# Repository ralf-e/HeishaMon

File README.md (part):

# HeishaMon mit Touch-Display

Dieser Fork ergänzt **HeishaMon Large / V6 (ESP32-S3)** um ein lokales Touch-Display. Die Erweiterung liegt auf dem Branch `touch-display`; `main` bleibt beim offiziellen HeishaMon-Stand.

- **Anzeige:** Waveshare 3,5-Zoll-IPS-Display (SKU 29318), 480 × 320 Pixel im Querformat. Die Übersicht zeigt 20 Werte, darunter Vorlauf/Rücklauf, Warmwasser und Heizkreise mit Ist-/Sollwerten, Volumenstrom und Wärmepumpenstatus.
- **Bedienung:** Per Touch durch alle WP-Topics, Zusatzdaten, Optional-PCB-Werte und Dallas-Sensoren blättern. Antippen öffnet Wertdetails; die Geräteinfo zeigt Modell- und Firmwaredaten. Fehlende und veraltete Daten werden gekennzeichnet.
- **Betriebsart:** „Automatisch“ oder „Listen only“ direkt am Display wählen und dauerhaft speichern. Bestehende Web-Einstellungen und Empfangsprüfungen bleiben wirksam. Das Display selbst erzeugt keine Wärmepumpen-Stellbefehle.
- **Aufbau:** Eine eigene Adapterplatine Rev.0.6 verbindet das Display mit der V6; optionales W5500-Ethernet ist weiterhin vorgesehen. Schaltplan, KiCad-Projekt und Fertigungsdaten liegen bei.

**Stand:** Software `0.1.0-dev.7`; [ESP32-S3-Build und Regressionstests erfolgreich](https://github.com/ralf-e/HeishaMon/actions/runs/40380596372). Hardwaretests, Passform und Stromreserve an der realen V6 stehen noch aus; die Firmware ist ein Entwicklungsstand.

**Weiterlesen:** [Touch-Dokumentation und Vorschau](touch-extension/README.md) · [Build, Installation und Updates im Fork](touch-extension/docs/Fork_Workflow.md)

**Neue Hardwarevariante:** [Adapter Rev.0.7 mit vier Spannungsmessungen](touch-extension/hardware/Rev07/README.md), weiterhin 23 × 41 mm. Rev.0.6 bleibt erhalten; die bisherige dev.7-Firmware wertet den neuen ADC noch nicht aus.

**Lizenz:** Die eigene Touch-Erweiterungssoftware steht unter [MPL-2.0](touch-extension/LICENSE); Geltungsbereich und Ausnahmen stehen in [LICENSING.md](touch-extension/LICENSING.md). Für HeishaMon selbst schlägt Upstream als Antwort auf [Issue #1029](https://github.com/heishamon/HeishaMon/issues/1029#issuecomment-6421009129) in [PR #1030](https://github.com/heishamon/HeishaMon/pull/1030) MPL-2.0 samt Drittlizenzhinweisen vor. Stand 26.10.2026 ist der PR noch offen. Einzelheiten stehen in den [Lizenzhinweisen zum Fork](touch-extension/docs/Fork_Workflow.md#prüfumfang-und-lizenz).

---

Die ursprüngliche HeishaMon-README folgt unten.

# Panasonic H, J, K & L Series Aquarea air-water heat pump protocol

This project makes it possible to read information from Panasonic Aquarea heat pump and report the data either to an MQTT server or as JSON format over HTTP.

Eine deutschsprachige [README_DE.md](README_DE.md) findest du hier. \
Een nederlandse vertaling [README_NL.md](README_NL.md) vind je hier. \
Suomen kielellä [README_FI.md](README_FI.md) luettavissa täällä.

*Help on translation to other languages is welcome.*

# Current releases
Latest release is available [here](https://github.com/Egyras/HeishaMon/releases). The ESP8266 compiled binary can be installed on a Wemos D1 mini, on the HeishaMon PCB and generally on any ESP8266 based board compatible with Wemos build settings (at least 4MB flash). You can also download the code and compile it yourself (see required libraries below). The ESP32-S3 binary is for the newer, large, version of heishamon.

# Using the software
HeishaMon is able to communicate with the Panasonic Aquarea H, J, K and L&series. [Confirmed by users types of HP you can find here](HeatPumpType.md) \
If you want to compile this image yourself be sure to use the mentioned libraries and support for a filesystem on the esp8266 so select the correct flash option in arduino ide for that.

When starting, without a configured wifi, an open-wifi-hotspot will be visible allowing you to configure your wifi network and your MQTT server. Configuration page will be located at http://192.168.4.1 . \

After configuring and booting the image will be able to read and talk to your heatpump. The GPIO13/GPIO15 connection will be used for communications so you can keep your computer/uploader connected to the board if you want. \
Serial 1 (GPIO2) can be used to connect another serial line (GND and TX from the board only) to read some debugging data.

All received data will be sent to different MQTT topics (see below for topic descriptions). There is also a 'panasonic_heat_pump/log' MQTT topic which provides debug logging and a hexdump of the received packets (if enabled in the web portal).

Some heatpumps (K/L series and newer) also send an additional "extra data block" with separate, more precise power consumption/production values. HeishaMon detects this automatically at boot and, if supported, publishes these as XTOP topics under 'panasonic_heat_pump/extra/...' (see [MQTT-Topics.md](MQTT-Topics.md) for the full list). If your heatpump doesn't support this extra data block, these topics simply won't appear. Note that on heatpumps that do support it, the "old" power topics (TOP15/16, TOP38-41, see MQTT-Topics.md) are no longer populated by the heatpump and will report bogus/invalid values (e.g. -200) — use the XTOP power values instead in that case.

You can connect a 1wire network on GPIO4 which will report in seperate MQTT topics (panasonic_heat_pump/1wire/sensorid).

The software is also able to measure Watt on a S0 port of two kWh meters. You only need to connect GPIO12 and GND to the S0 of one kWh meter and if you need a second kWh meter use GPIO14 and GND. It will report on MQTT topic panasonic_heat_pump/s0/Watt/1 and panasonic_heat_pump/s0/Watt/2 and also in the JSON output. You can replace 'Watt' in the previous topic with 'Watthour' to get consumption counter in WattHour (per mqtt message) or to 'WatthourTotal' to get the total consumption measured in WattHour. To sync the WatthourTotal with your kWh-meter, publish the correct value to MQTT to the panasonic_heat_pump/s0/WatthourTotal/1 or panasonic_heat_pump/s0/WatthourTotal/2 topic with the 'retain' option while heishamon is rebooting. Upon reboot, heishamon reads this value as the last known value to you can sync using this method.

Updating the firmware is as easy as going to the firmware menu and, after authentication with username 'admin' and password 'heisha' (or other provided during setup), uploading the binary there.

A json output of all received data (heatpump and 1wire) is available at the url http://heishamon.local/json (replace heishamon.local with the ip address of your heishamon device if MDNS is not working for you).

Within the 'integrations' folder you can find examples how to connect your automation platform to the HeishaMon.

# Rules functionality
The rules functionality allows you to control the heatpump from within the HeishaMon itself. Which makes it much more reliable then having to deal with external domotica over WiFi. When posting a new ruleset, it is immidiatly validated and when valid used. When a new ruleset is invalid it will be ignored and the old ruleset will be loaded again. You can check the console for feedback on this. If somehow a new valid ruleset crashes the HeishaMon, it will be automatically disabled the next reboot, allowing you to make changes. This prevents the HeishaMon getting into a boot loop.

The techniques used in the rule library allows you to work with very large rulesets, but best practice is to keep it below 10.000 bytes.

Notice that sending commands to the heatpump is done asynced. So, commands sent to the heatpump at the beginning of your syntax will not immediatly be reflected in the values from the heatpump later on. Therefor, heatpump values should be read from the heatpump itself instead of those based on the values you keep yourself.

## Syntax
Two general rules are that spaces are mandatory and semicolons are used as end-of-line character.

### Variables
The ruleset uses the following variable structure:

- `#`: Globals
These variables can be accessed throughout the ruleset but have to defined inside a rule block. Don't use globals for all your variables, because it will persistently use memory.

- `$`: Locals
These variables live inside a rule block. When a rule block finishes, these variables will be cleaned up, freeing any memory used.

- `@`: Heatpump parameters
These are the same as listed in the Manage Topics documentation page and as found on the HeishaMon homepage. The ruleset also follows the R/W logic as used through the MQTT and REST API. That means that the read topics differ from the write topics. So reading the heatpump state is done through `@Heatpump_State`, changing the heatpump state through `@SetHeatpump`.

- `%`: Datetime variables
These can be used for date and time based rules. Currently `%hour` (0 - 23), `%minute` (0 - 59), `%month` (1 - 12), and `%day` (1 - 7)  are supported. All are plain integers. A proper NTP configuration is needed to set the correct system date and time on the HeishaMon.

- `?`: Thermostat parameters
These variables reflect parameters read from the connected thermostat when using the OpenTherm functionality. When OpenTherm is supported this documentation will be extended with more precise information. The can check the opentherm tab for the variables that can be used. The names are the same for reading and writing, but not all values support reading and/or writing. The opentherm tab also lists this.

- `ds18b20#2800000000000000`: Dallas 1-wire temperature values
Use these variables to read the temperature of the connected sensors. These values are of course readonly. The id of the sensor should be placed after the hashtag.

- `s0#watt[hour[total]]_?`: The S0 values for port 1 and 2. Replace the question mark with the port number.
For example s0#watt_1 to get watt from port 1 and s0#watthourtotal_2 to get total watthours from port 2

When a variable is called but not yet set to a value, the value will be `NULL`.

Variables can be of boolean (`1` or `0`), float (`3.14`), integer (`10`), and string type. Defining strings is done with single or double quotes.

### Events or functions
Rules are written in `event` or `function` blocks. These are blocks that are triggered when something happened; either a new heatpump or thermostat value has been received or a timer fired. Or can be used as plain functions

```
on [event] then
  [...]
end

on [name] then
  [...]
end
```

Events can be Heatpump or thermostat parameters or timers:
```
on @Heatpump_State then
  [...]
end

on ?setpoint then
  [...]
end

on timer=1 then
  [...]
end
```

When defining functions, you just name your block and then you can call it from anywhere else:
```
on foobar then
  [...]
end

on @Heatpump_State then
  foobar();
end
```

Functions can have parameters which you can call:
```
on foobar($a, $b, $c) then
  [...]

on @Heatpump_State then
  foobar(1, 2, 3);
end
```

If you call a function less values then the function takes, all other parameters will have a NULL value.

There is currently one special function that calls when the system is booted on when a new ruleset is saved:
```
on System#Boot then
  [...]
end
```

This special function can be used to initially set your globals or certain timers.

### Operators
Regular operators are supported with their standard associativity and precedence. This allows you to also use regular math.
- `&&`: And
- `||`: Or
- `==`: Equals`
- `!=`: Not Equals`
- `>=`: Greater or equal then
- `>`: Greater then
- `<`: Lesser then
- `<=`: Lesser or equal then
- `-`: Minus
- `%`: Modulus
- `*`: Multiply
- `/`: Divide
- `+`: Plus
- `^`: Power

Parenthesis can be used to prioritize operators as it would work in regular math.

### Functions
- `coalesce`
Returns the first value not `NULL`. E.g., `$b = NULL; $a = coalesce($b, 1);` will return 1. This function accepts an unlimited number of arguments.

- `max`
Returns the maximum value of the input parameters.

- `min`
Returns the minimum value of the input parameters.

- `isset`
Returns `1` when the input variable has a numeric value and `0` when it is still `NULL` (a string value also returns `0`). Use it to test for `NULL`: a comparison with `NULL` (e.g. `#g == NULL`) always results in `NULL`, which is false, so write `if isset(#g) == 0 then` instead.

- `round`
Rounds the input float to the nearest integer.

- `floor`
The largest integer value less than or equal to the input float.

- `ceil`
The smallest integer value greater than or equal to the input float.

- `setTimer`
Sets a timer to trigger in X seconds. The first parameter is the timer number and the second parameters the number of seconds before it fires. A timer only fires once so it has to be re-set for recurring events. When a timer triggers it will can the timer event as described above. E.g.

- `print`
Prints a value to the console.

- `concat`
Concatenates various values into a combined string. E.g.: `@SetCurves = concat('{zone1:{heat:{target:{high:', @Z1_Heat_Curve_Target_High_Temp, ',low:32}}}}');`

- `gpio`
Allows setting or getting a GPIO state. When called with a single argument, a GPIO state is returned. When called with two arguments the state of a GPIO is set. This function only sets digital pins so the state can only be 0 or 1. The two relays on the large heishamon are gpio21 and gpio47. See the example to switch them each two seconds.

```
on System#Boot then
   setTimer(10, 2);
end

on timer=10 then
   setTimer(20, 2);
   gpio(21,0);
   gpio(47,1);
end

on timer=20 then
   setTimer(10, 2);
   gpio(21,1);
   gpio(47,0);
end
```

### Conditions
The only supported conditions are `if`, `else`, and `elseif`:

```
if [condition] then
  [...]
else
  if [condition] then
    [...]
  end
end
```

```
if [condition] then
  [...]
elseif [condition] then
  if [condition] then
    [...]
  else
    [...]
  end
elseif [condition] then
  [...]
else
  [...]
end
```

### Examples
Complete, documented example rulesets live in [`Examples/Rules/`](Examples/Rules/) — each comes with a README explaining its design and a `tests/` directory of regression scenarios. The scenarios run on your PC (no device needed) through the host-side harness in [`Examples/Rules/harness/`](Examples/Rules/harness/), which compiles the real HeishaMon rules engine with plain `g++` and performs the same validation as an on-device upload, then simulates topic changes and timers while checking the commands your ruleset sends. Run all tests with `Examples/Rules/run_tests.sh`, or validate your own ruleset before uploading with `harness/harness <rules.txt> parse` — see the harness README for the scenario language.

Once the rules system is in used by more and more users, additional examples will be added to the documentation.

*Calculating WAR*
```
on calcWar($Ta1, $Tb1, $Ta2, $Tb2) then
	#maxTa = $Ta1;

	if @Outside_Temp >= $Tb1 then
		#maxTa = $Ta1;
	elseif @Outside_Temp <= $Tb2 then
		#maxTa = $Ta2;
	else
		#maxTa = $Ta1 + (($Tb1 - @Outside_Temp) * ($Ta2 - $Ta1) / ($Tb1 - $Tb2));
	end
end
```

*Thermostat setpoint*
```
on ?roomTemp then
	calcWar(32, 14, 41, -4);

	$margin = 0.25;

	if ?roomTemp > (?roomTempSet + $margin) then
		if @Heatpump_State == 1 then
			@SetHeatpump = 0;
		end
	elseif ?roomTemp < (?roomTempSet - $margin) then
		if @Heatpump_State == 0 then
			@SetHeatpump = 1;
		end
	else
		@SetZ1HeatRequestTemperature = round(#maxTa);
	end
end
```

# Factory reset
A factory reset can be performed on the web interface. If the web interface is unavailable (not wifi or other reason) you can perform a hard factory reset. With recent firwmare you just hold the boot/flash button for more than 10 seconds. With older firmware you most do a double reset. This double reset should be performed not too fast but also not too slow. Usually halve a second between both resets should do the trick. To indicate that the double reset performed a factory reset, the blue led will flash rapidly (You need to press reset again now to restart HeishaMon back to normal where a WiFi hotspot should be visible again).

# Further information
Below you can find some technical details about the project. How to build your own cables. How to build your own PCB etc.

## Connection details:
Communication can be established thru one of the two sockets: CN-CNT or CN-NMODE. If you have an existing Panasonic CZ-TAW1 WiFi interface that you want to replace with HeishaMon, it is only a matter of plugging the cable out from CZ-TAW1 and reconnecting to your HeishaMon device. However it is not possible to use HeishaMon and the original CZ-TAW1 module together as an active device. It is however possible to put HeishaMon on "Listen Only" mode which will allow HeishaMon and the original CZ-TAW1 module to co-exist. The only downside to this is that HeishaMon is unable to send commands and use the optional PCB option.

Communication parameters: TTL 5V UART 9600,8,E,1  \
 \
CN-CNT Pin-out (from top to bottom) \
1 - +5V (250mA)  \
2 - 0-5V TX (from heatpump) \
3 - 0-5V RX (to heatpump)\
4 - +12V (250mA) \
5 - GND \
 \
CN-NMODE Pin-out (from left to right) \
"Warning! As printed on the PCB, the left pin is pin 4 and right pin is pin 1. Do not count 1 to 4 from left!  \
4 - +5V (250mA)  \
3 - 0-5V TX (from heatpump) \
2 - 0-5V RX (to heatpump) \
1 - GND

HeishaMon will receive power from the Panasonic over the cable (5v power).

## Long distance connection
It it possible to connect the HeishaMon over a long distance. Up to 5 meter is working with normal cabling. For longer distances a TTL-to-RS485 configuration as show in the picture below is possible. The however requires HeishaMon to be powered externally using 5v power (for example from an USB cable).

## Where to get connectors
[RS-Online orders](Connectors_RSO.md)

[Conrad orders](Connectors_Conrad.md)

Use some 24 AWG shielded 4-conductors cable.

## The HeishaMon hardware itself
The PCB needed to connect to the heatpump is just a ESP8266 or a ESP32 (for the Heishamon Large it uses the ESP32-S3-MINI-1-N4R2) with some level shifting to get the 5v tx/rx down down 3.3v. That is the only thing to make it work.
For the ESP8266 the Heishamon software uses the schematic as described in the [ESP8266 hardware design guide](https://documentation.espressif.com/esp8266_hardware_design_guidelines_en.pdf) figure 1-10c on page 12. The GPIO5 shown there is the enable on boot (or disabled when listen only is selected). But it is also possible to user a proper schmitt buffer instead of basic level shifting.
The rest of Heishamon software is just adding more stuff, like Dallas 1wire, Opentherm etc.

To make things easy you can order a completed PCB from some project members: \
[Lectronz shop](https://lectronz.com/products/heishamon-communication-pcb) from Igor Ybema (aka TheHogNL) based in the Netherlands

## Building the arduino image yourself
boards: \
esp8266 by esp8266 community version 3.0.2 [Arduino](https://github.com/esp8266/Arduino/releases/tag/3.0.2)

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
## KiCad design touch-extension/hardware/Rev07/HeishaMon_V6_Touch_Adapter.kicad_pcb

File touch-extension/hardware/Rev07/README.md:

# Adapter Rev.0.7 - vier Spannungsmessungen

Neue Hardwarevariante neben der unveränderten Rev.0.6. Zielmaß weiterhin **23 × 41 mm**, zwei Kupferlagen, 1,6 mm. Stecker J1/J2/J3/J4 und die Überkopf-Einbaulage bleiben erhalten. Alle SMD-Bauteile liegen auf F (montiert unten); die vorhandenen manuellen Stiftleisten auf B.

## Messkanäle

| ADS1115-Eingang | Messpunkt | Spannungsteiler oben / unten | Vorgesehener Eingangsbereich |
| --- | --- | --- | --- |
| AIN0 | 3,3 V direkt an der V6, vor R0 | 10 kΩ / 10 kΩ | 0–3,6 V |
| AIN1 | 3,3 V im Erweiterungszweig, hinter R0 | 10 kΩ / 10 kΩ | 0–3,6 V |
| AIN2 | 5-V-Versorgung der V6 | 20 kΩ / 10 kΩ | 0–5,5 V |
| AIN3 | Externer 12-V-Messanschluss TP5 | 68 kΩ / 10 kΩ | 0–18 V, positiv gegen GND |

Die vorhandene Adapterbelegung führt keine 12 V. Für die Messung genügt bei gemeinsamer V6-/Adaptermasse **eine zusätzliche Leitung vom 12-V-Abgriff zu TP5 (+12V_SENSE)**. Die Masseverbindung besteht bereits über die vorhandenen Steckkontakte; eine zusätzliche Masseleitung ist dann nicht erforderlich. **TP6 ist ein optionaler GND-Löt- und Prüfpunkt**, beispielsweise für die Multimeter-Messspitze oder einen separaten Prüfaufbau ohne vorhandene Masseverbindung. TP5 ist ausschließlich ein hochohmiger Messeingang und versorgt die Platine nicht. Der konkrete 12-V-Abgriff muss am eigenen Gerät identifiziert werden. Keine Netzspannung, keine 24 V und keine negative Spannung anschließen.

## ADC und Schutzbeschaltung

- U2: ADS1115IDGSR, VSSOP-10, I²C-Adresse **0x48**, Versorgung aus +3V3_EXT. Der vorhandene Bus mit MCP23008 (0x20) und Touch (0x38) wird mitbenutzt; keine weiteren ESP32-Pins nötig.
- U1 verwendet in dieser Revision den **MCP23008-E/SS im SSOP-20-Gehäuse**. Das spart gegenüber dem bisherigen SOIC-18 Platz für die Messschaltung. Der Baustein ist elektrisch funktionsgleich, hat aber eine andere physische Pinbelegung; SOIC- und SSOP-Teile sind nicht austauschbar.
- U3: TMUX1511PWR, vier analoge Schalter mit Schutz bei ausgeschalteter Versorgung. Die Spannungsteiler liegen vor den Schaltern; dadurch sehen deren Eingänge auch bei anliegenden 12 V nur die heruntergeteilte Spannung.
- U4: TLV809EA29DCKR, 2,93-V-Supervisor. Er gibt die Messpfade erst bei ausreichender Erweiterungsversorgung frei und trennt sie bei Unterspannung. MCP23008 **GP0** liest dieses Freigabesignal: Low bedeutet ungültige Messung. GPIO5 / TX-Freigabe bleibt davon getrennt.
- Jeder Kanal hat einen 100-nF-Filter vor dem Schalter, danach einen 1-kΩ-Serienwiderstand und einen **100-kΩ-Ableitwiderstand** am ADC-Eingang. Neue Messwiderstände: 0603, 0,1 %. Bei der Bestellprüfung wurden die zuvor vorgesehenen 1 MΩ auf 100 kΩ geändert, damit der maximal spezifizierte Powered-off-Leckstrom rechnerisch unter 0,3 V am ausgeschalteten ADC bleibt. Die Belastung durch Serien-/Ableitwiderstände muss bei der Umrechnung berücksichtigt werden; die Faktoren stehen in `validation_summary.json`.
- Die digitalen Versorgungsprüfungen und die Hardware-Isolation sind kein Ersatz für einen Überspannungsschutz gegen beliebige Fehlverdrahtung. Unterhalb der Freigabeschwelle werden keine gültigen Spannungswerte geliefert; Ausfall von ESP32/Versorgung kann nicht am abgeschalteten Display angezeigt werden.

Die Messung dient langsamer Versorgungskontrolle. Gegen Multimeter kalibrieren; sehr kurze Einbrüche und die Regler-Stromreserve sind damit nicht zuverlässig nachgewiesen. Der ADS1115-Eingangswiderstand und die temperaturabhängigen Leckströme sind zusätzlich zur Widerstandstoleranz zu berücksichtigen.

Für die spätere Firmware: alle vier Kanäle single-ended gegen GND, PGA-Messbereich **±4,096 V**, beispielsweise 128 Samples/s und gefilterte langsame Anzeige. Bei Low an GP0 die Messung als ungültig kennzeichnen. Die nominalen Umrechnungsfaktoren stehen in `validation_summary.json`; sie berücksichtigen die 1-kΩ-/100-kΩ-Beschaltung, ersetzen aber keinen Abgleich am Gerät.

## Ergebnis der elektrischen Prüfungen

ERC **0**, DRC **0**, **0 offene Verbindungen**. Unabhängiger Vergleich: 35 Netze im Schaltplan und auf den echten PCB-Pads, unveränderte Steckerpositionen J1/J2/J3/J4. 51 PCB-Footprints: 42 SMD-Bauteile, drei manuelle Stiftleisten und sechs Mess-/Lötpads. Zwei Kupferlagen, 835 Leiterbahnsegmente und 79 Vias.

Die kompakte Variante verwendet mindestens 0,15 mm Leiterbahnbreite und Kupferabstand sowie Vias 0,50/0,20 mm. Der Kantenabstand bleibt mindestens 0,30 mm. Die zugehörigen Prototyp-Fertigungsdaten liegen unter [manufacturing/JLCPCB/Rev07](../../manufacturing/JLCPCB/Rev07/README.md). Die [Bestellprüfung](Bestellpruefung.md) dokumentiert den aktuellen Bestand aller 18 SMD-Typen und den nummerierten Lieferanten-Padvergleich. U4 wurde auf CPL180 korrigiert; U1/U2/U3/J4 verwenden CPL270. Hersteller-Preview/Zentrierung sowie reale V6-Kontakte und Passform bleiben offen. Dies ist keine Hardware- oder Bestellfreigabe.

## Software und Prüfumfang

Die vorhandene Firmware **0.1.0-dev.7 / Commit d19d576** bleibt für Rev.0.6 verfügbar. Sie liest den neuen ADC noch nicht aus. Die bisherige Display-/Betriebsartenfunktion wird durch die zusätzlichen I²C-Bauteile nicht absichtlich verändert; der reale Betrieb beider Platinenrevisionen ist noch zu prüfen. Für Spannungsanzeige/MQTT ist eine separate Firmware-Erweiterung erforderlich.

Vor Fertigung müssen ERC, DRC, Verbindungsvergleich, 12-V-Polarität, Montageabstände, Bestückungsorientierung und Bauteilverfügbarkeit geprüft sein. Der elektrische Rechencheck ersetzt keine Hardwareprüfung. Es erfolgt keine automatische Fertigungsfreigabe oder Bestellung.

## Reproduktion

1. `tools/design_adapter.py --voltage` mit KiCad-Python erzeugt diese Variante, ohne Rev.0.6 zu überschreiben. Die festgehaltene Platzierung steht in `component_placement.json`.
2. Für die Reproduktion des vorhandenen Layouts `tools/route_voltage_monitor.py restore` verwenden. Es übernimmt die festgehaltene endgültige Kupfergeometrie aus `routed_copper.json` und füllt die Masseflächen. Dafür ist kein Autorouter erforderlich.
3. Nur für eine neue Entflechtung: `tools/route_voltage_monitor.py export` erzeugt die lokale DSN-Datei unter `tmp/Rev07/`; lokal mit Freerouting entflechten und anschließend mit `import` übernehmen. Nicht jeden Autorouter-Ausgang als fertiges Layout behandeln: Auch minimale Verengungen und lose Enden mit KiCad prüfen und korrigieren.
4. KiCad ERC, DRC und XML-Netzliste neu exportieren; danach `tools/check_voltage_monitor.py` mit KiCad-Python ausführen. Die unabhängige Prüfung vergleicht Schaltplan und echte PCB-Pads, Steckerpositionen und Messbereichsrechnung.

## Quellen

- [ADS1115: Datenblatt und Pinbelegung](https://www.ti.com/lit/ds/symlink/ads1115.pdf)
- [TMUX1511: Datenblatt, Powered-off Protection](https://www.ti.com/lit/ds/symlink/tmux1511.pdf)
- [TLV809E: 2,93-V-Supervisor und SC70-Pinbelegung](https://www.ti.com/lit/ds/symlink/tlv803e.pdf)

Die Dateien im übergeordneten `hardware/` und unter `manufacturing/JLCPCB/Rev06/` beschreiben weiterhin Rev.0.6. Sie dürfen für die neue Messvariante nicht mit Rev.0.7-Dateien vermischt werden.

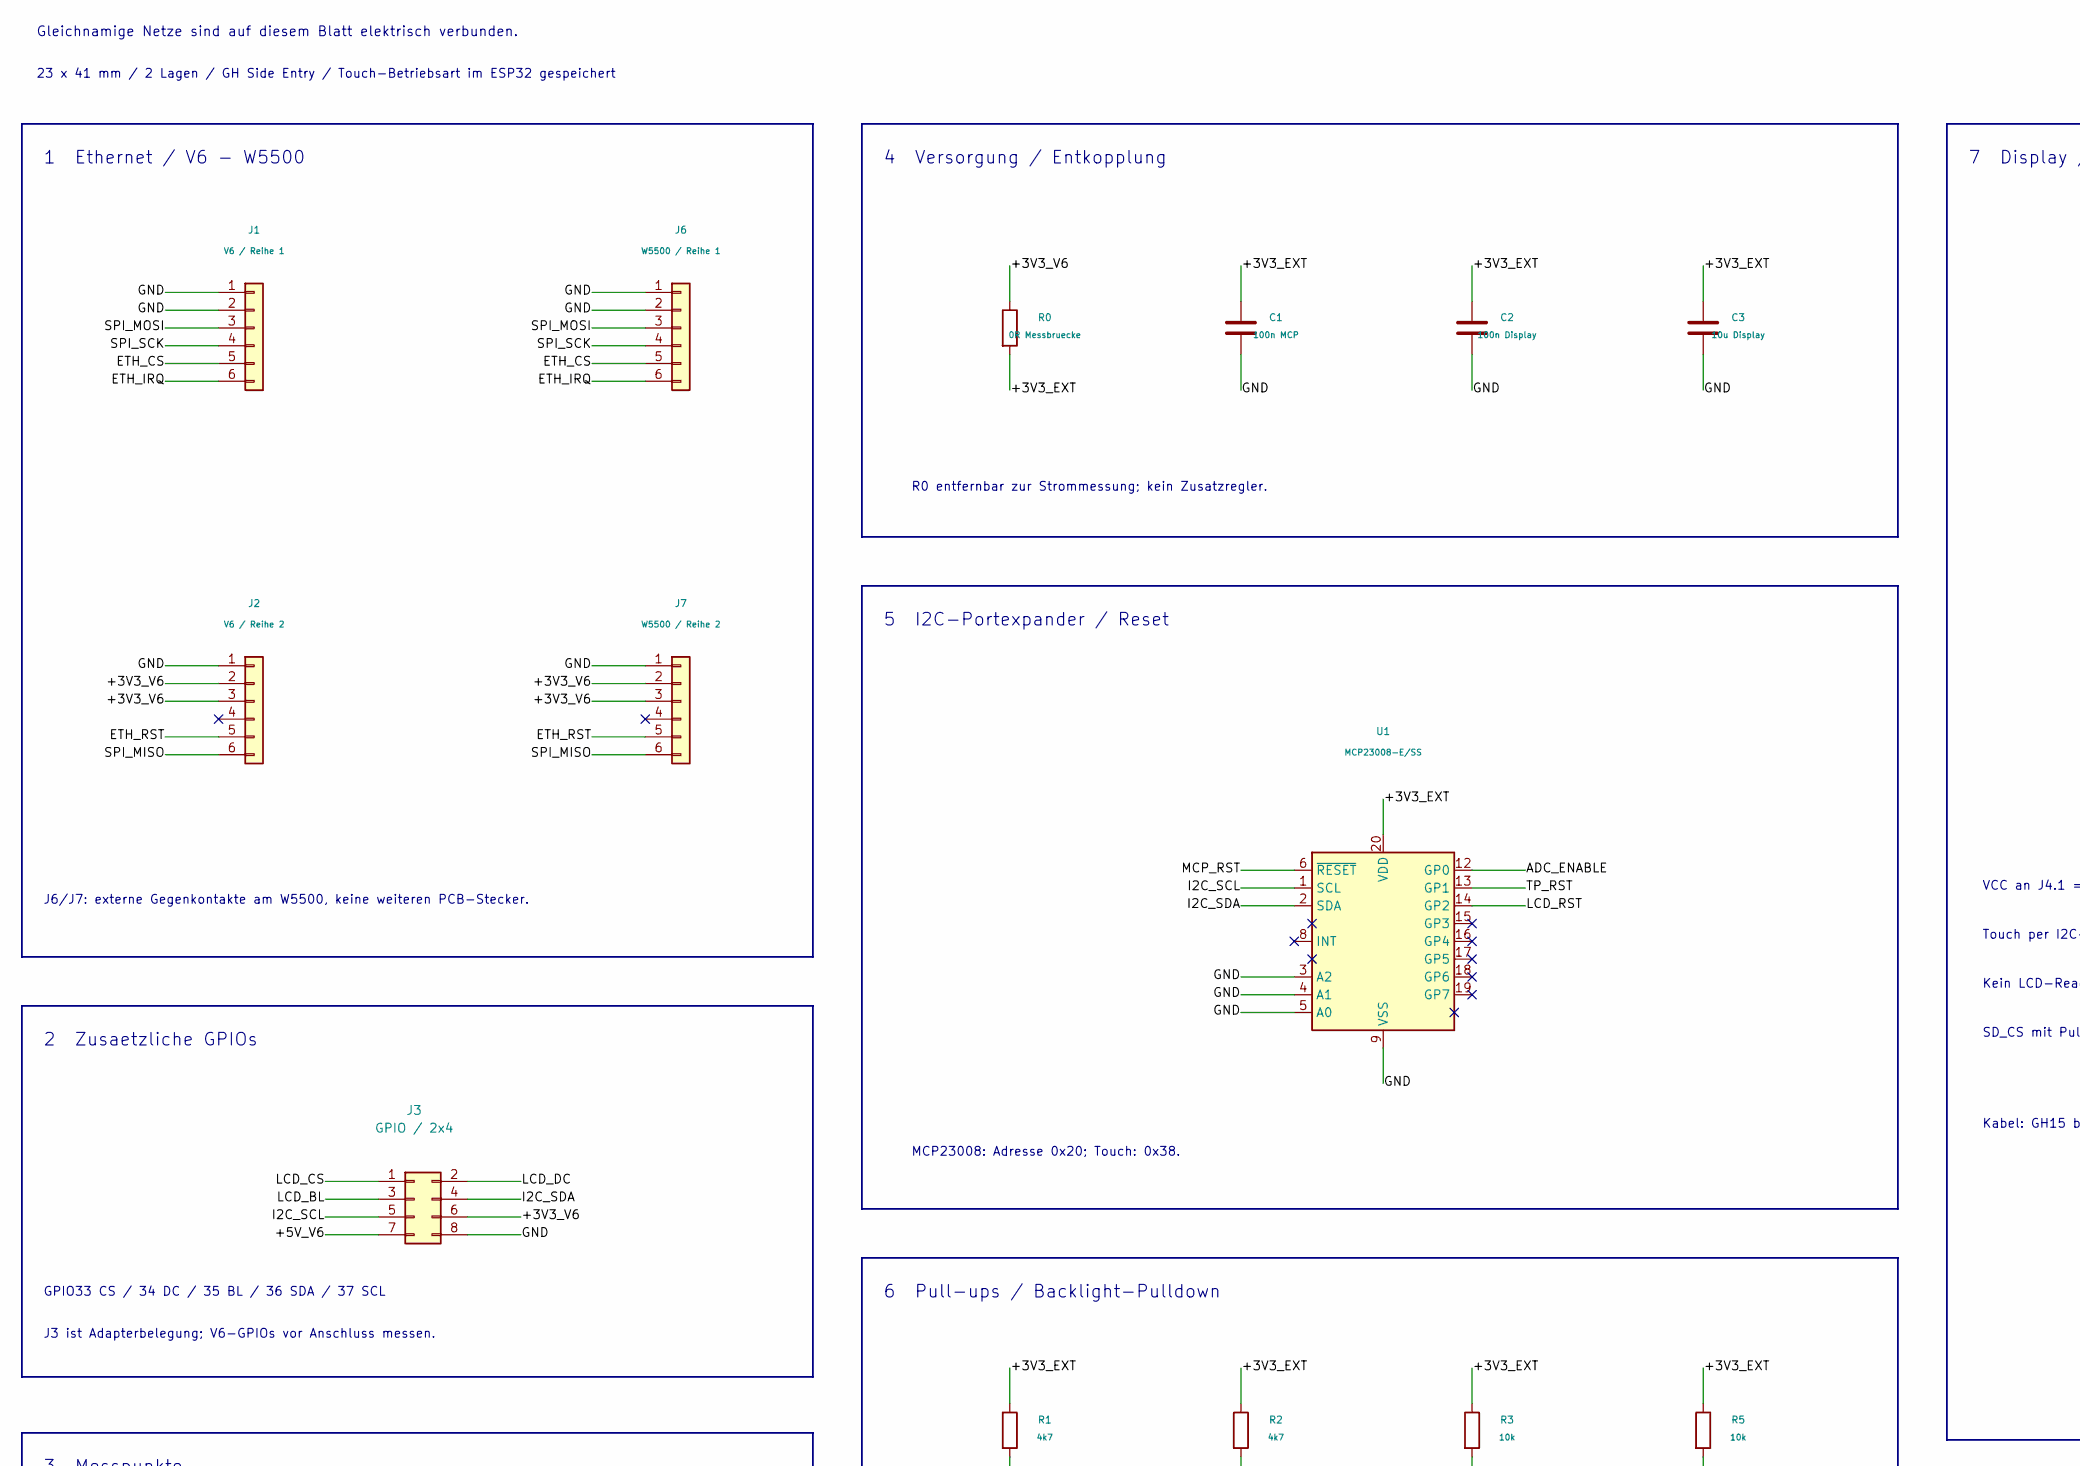
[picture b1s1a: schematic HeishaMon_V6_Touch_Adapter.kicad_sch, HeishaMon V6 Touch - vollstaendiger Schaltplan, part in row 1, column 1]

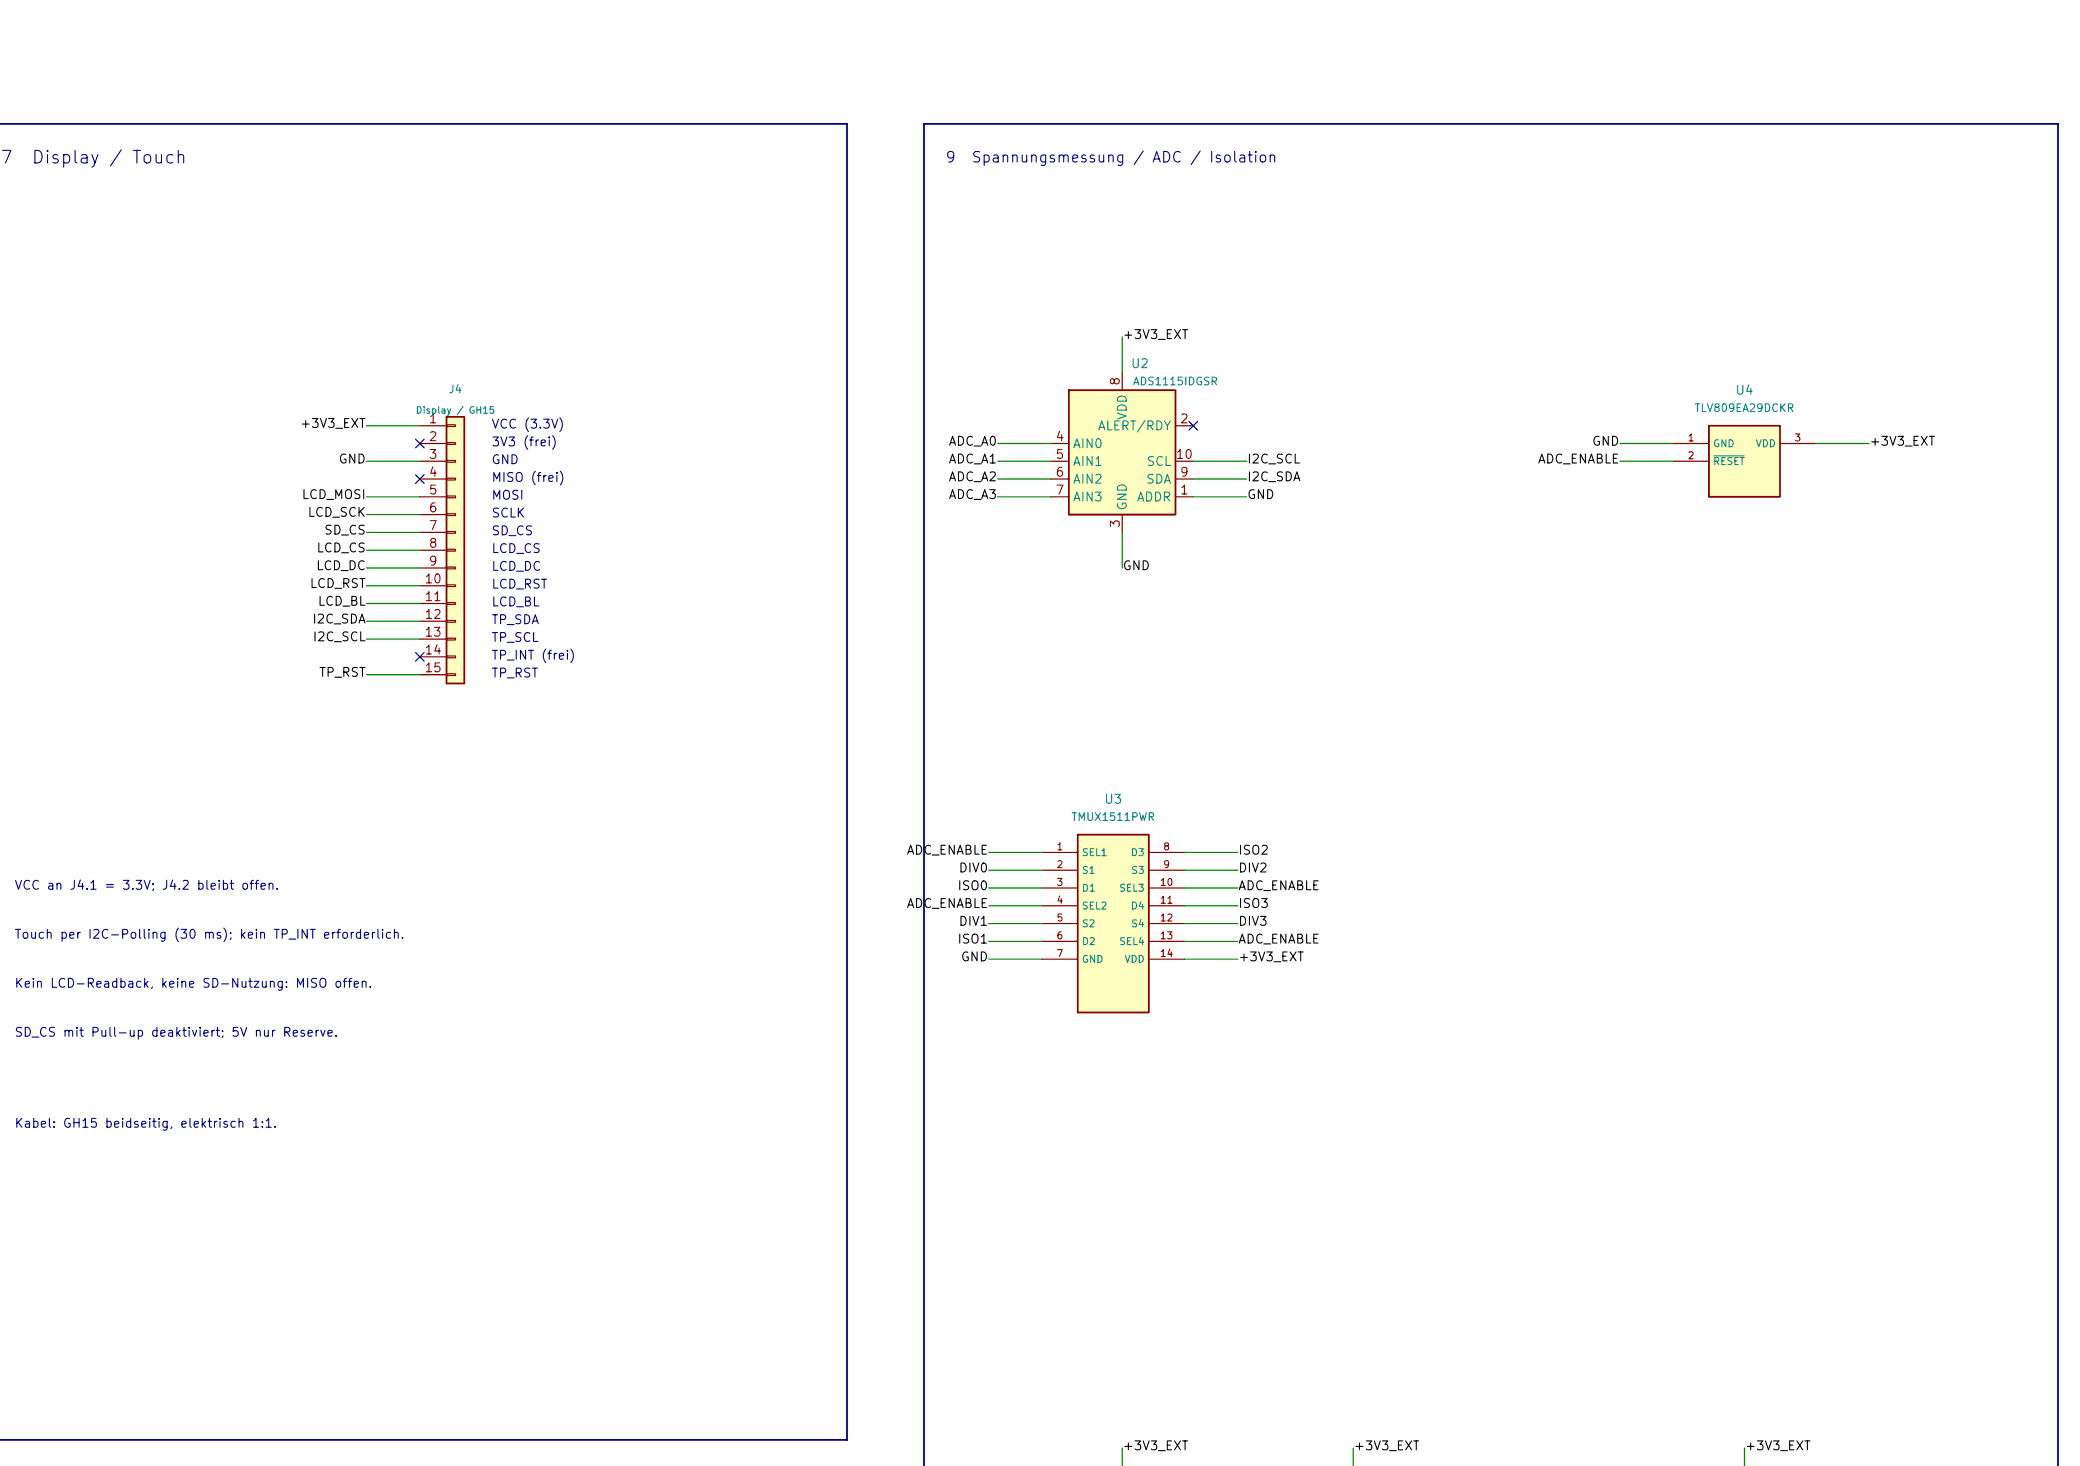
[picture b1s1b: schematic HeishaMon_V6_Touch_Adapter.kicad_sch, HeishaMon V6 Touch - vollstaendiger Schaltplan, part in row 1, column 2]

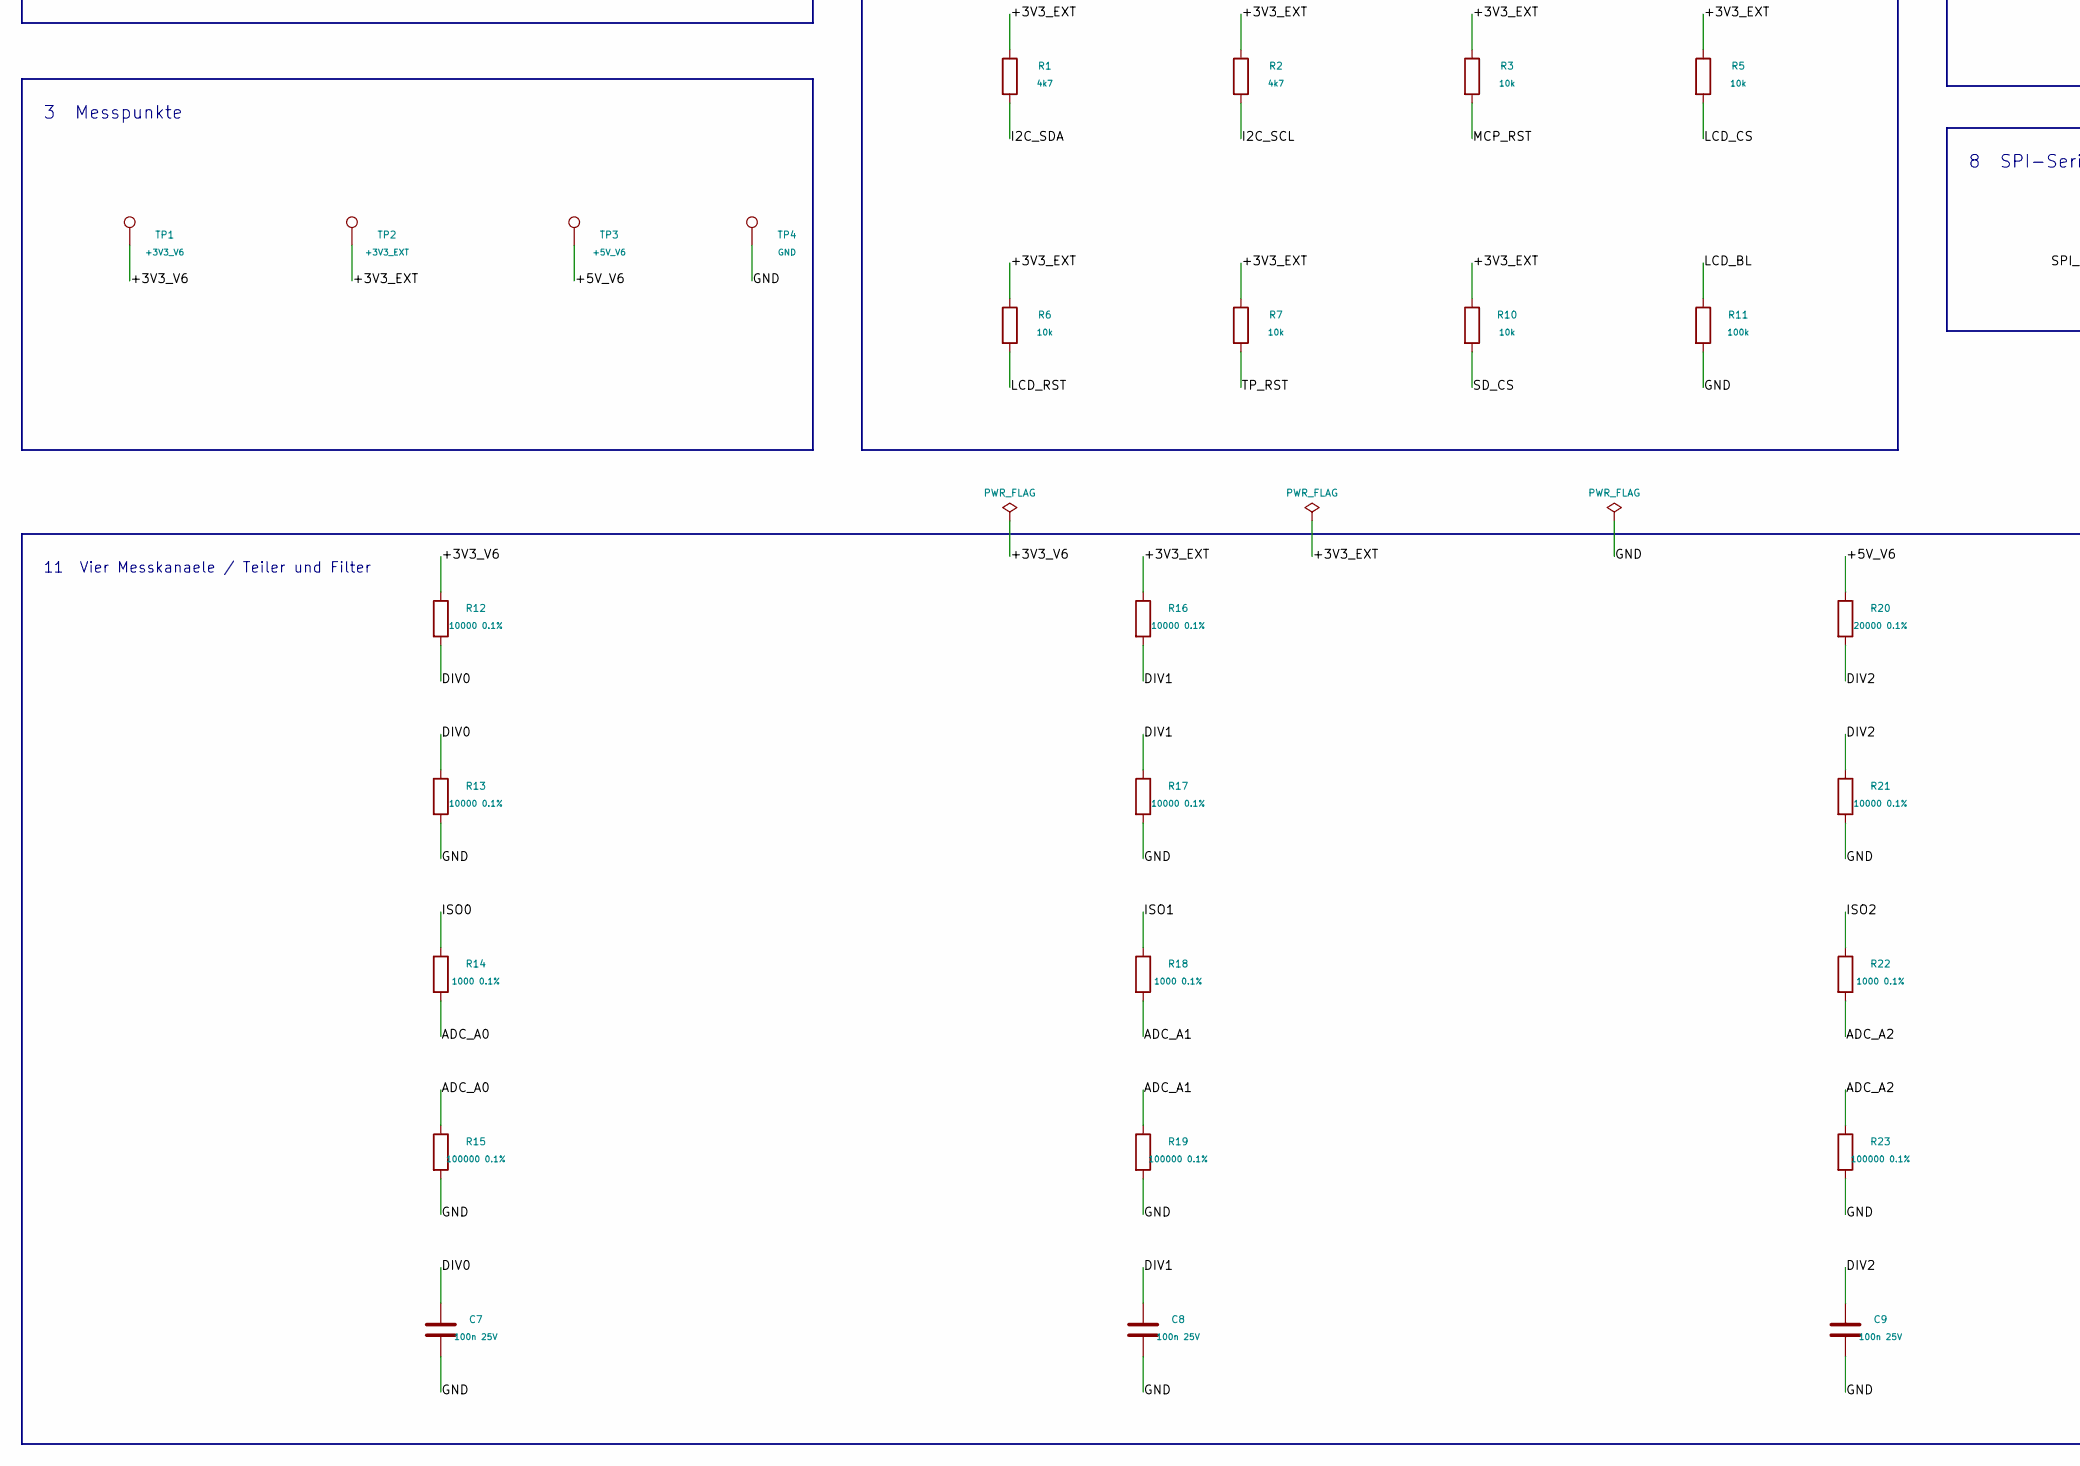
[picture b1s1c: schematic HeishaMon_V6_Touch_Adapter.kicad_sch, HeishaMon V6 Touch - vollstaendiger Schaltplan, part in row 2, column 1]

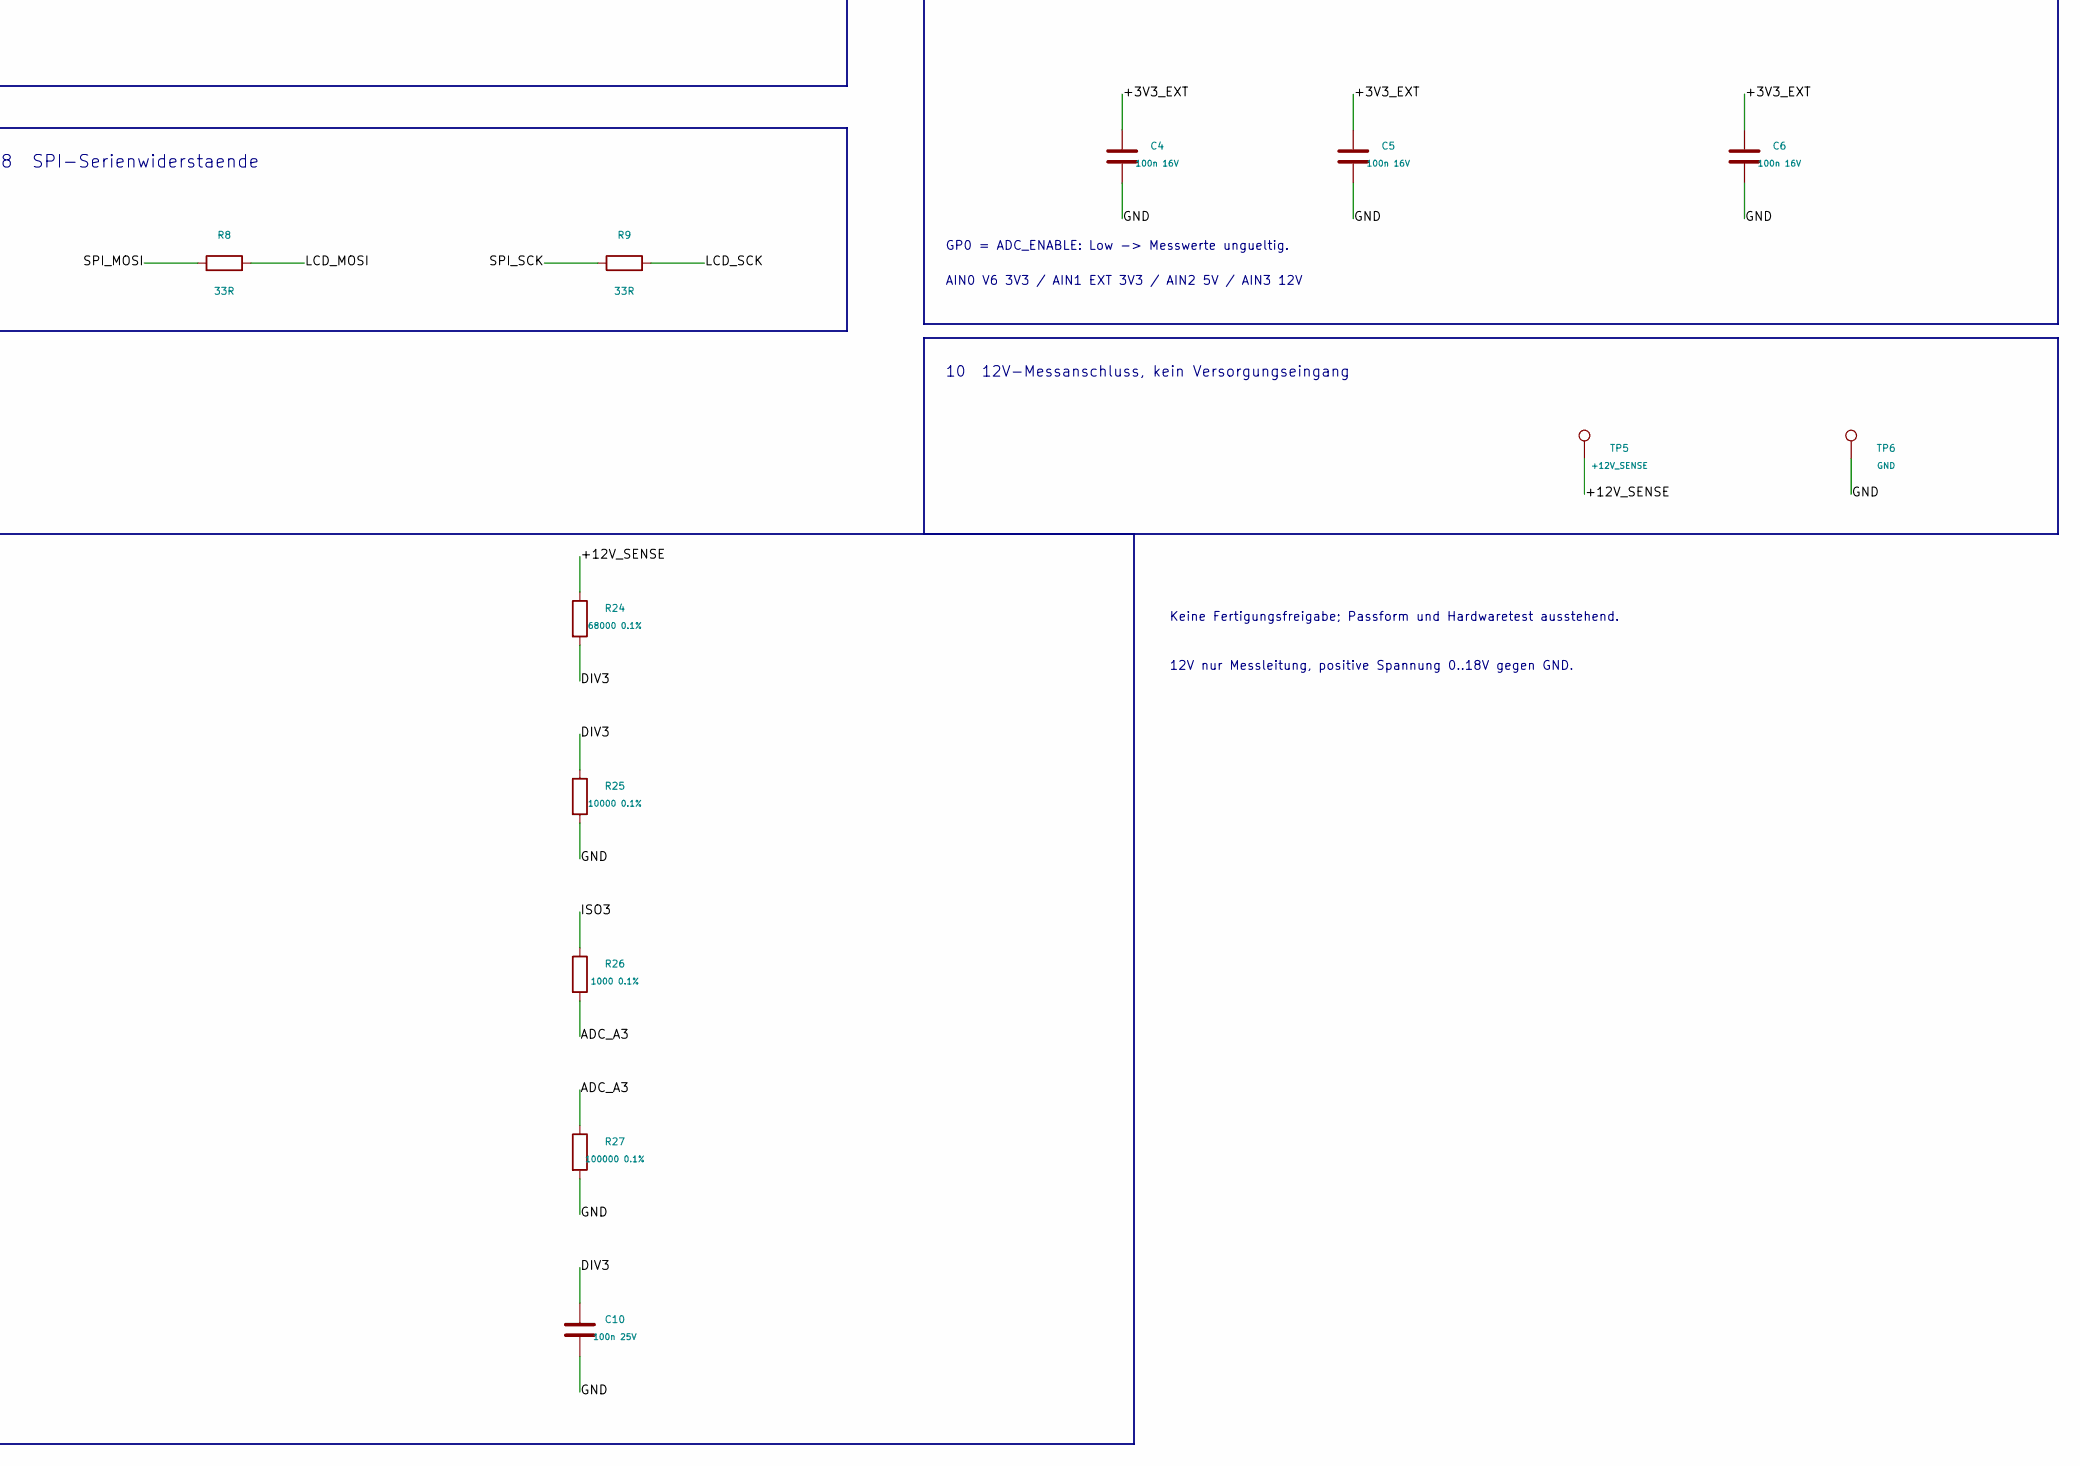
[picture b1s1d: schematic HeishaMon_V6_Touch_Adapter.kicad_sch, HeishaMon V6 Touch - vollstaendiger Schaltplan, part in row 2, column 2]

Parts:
C1: 100n MCP; C_0805_2012Metric
C2: 100n Display; C_0805_2012Metric
C3: 10u Display; C_0805_2012Metric
C4, C5, C6: 100n 16V; C_0603_1608Metric
C7, C8, C9, C10: 100n 25V; C_0603_1608Metric
J1: V6 / Reihe 1; PinHeader_1x06_P2.54mm_Vertical
J2: V6 / Reihe 2; PinHeader_1x06_P2.54mm_Vertical
J3: GPIO / 2x4; PinHeader_2x04_P2.54mm_Vertical
J4: Display / GH15; JST_GH_SM15B-GHS-TB_1x15-1MP_P1.25mm_Horizontal
J6: W5500 / Reihe 1
J7: W5500 / Reihe 2
R0: 0R Messbruecke; R_0805_2012Metric
R1, R2: 4k7; R_0805_2012Metric
R3, R5, R6, R7, R10: 10k; R_0805_2012Metric
R8, R9: 33R; R_0805_2012Metric
R11: 100k; R_0805_2012Metric
R12, R13, R16, R17, R21, R25: 10000 0.1%; R_0603_1608Metric
R14, R18, R22, R26: 1000 0.1%; R_0603_1608Metric
R15, R19, R23, R27: 100000 0.1%; R_0603_1608Metric
R20: 20000 0.1%; R_0603_1608Metric
R24: 68000 0.1%; R_0603_1608Metric
TP1: +3V3_V6; TestPoint_Pad_D1.0mm
TP2: +3V3_EXT; TestPoint_Pad_D1.0mm
TP3: +5V_V6; TestPoint_Pad_D1.0mm
TP4: GND; TestPoint_Pad_D1.0mm
TP5: +12V_SENSE; TestPoint_THTPad_D1.5mm_Drill0.7mm
TP6: GND; TestPoint_THTPad_D1.5mm_Drill0.7mm
U1: MCP23008-E/SS; SSOP-20_5.3x7.2mm_P0.65mm
U2: ADS1115IDGSR; TSSOP-10_3x3mm_P0.5mm
U3: TMUX1511PWR; TSSOP-14_4.4x5mm_P0.65mm
U4: TLV809EA29DCKR; SOT-323_SC-70

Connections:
+3V3_EXT: C1.1, C2.1, C3.1, C4.1, C5.1, C6.1, J4.1, R0.2, R1.1, R2.1, R3.1, R5.1, R6.1, R7.1, R10.1, R16.1, TP2.1, U1.20 (VDD), U2.8 (VDD), U3.14 (VDD), U4.3 (VDD)
+3V3_V6: J2.2, J2.3, J3.6, J7.2, J7.3, R0.1, R12.1, TP1.1
+5V_V6: J3.7, R20.1, TP3.1
+12V_SENSE: R24.1, TP5.1
ADC_A0: R14.2, R15.1, U2.4 (AIN0)
ADC_A1: R18.2, R19.1, U2.5 (AIN1)
ADC_A2: R22.2, R23.1, U2.6 (AIN2)
ADC_A3: R26.2, R27.1, U2.7 (AIN3)
ADC_ENABLE: U1.12 (GP0), U3.1 (SEL1), U3.4 (SEL2), U3.10 (SEL3), U3.13 (SEL4), U4.2 (~RESET)
DIV0: C7.1, R12.2, R13.1, U3.2 (S1)
DIV1: C8.1, R16.2, R17.1, U3.5 (S2)
DIV2: C9.1, R20.2, R21.1, U3.9 (S3)
DIV3: C10.1, R24.2, R25.1, U3.12 (S4)
ETH_CS: J1.5, J6.5
ETH_IRQ: J1.6, J6.6
ETH_RST: J2.5, J7.5
GND: C1.2, C2.2, C3.2, C4.2, C5.2, C6.2, C7.2, C8.2, C9.2, C10.2, J1.1, J1.2, J2.1, J3.8, J4.3, J6.1, J6.2, J7.1, R11.2, R13.2, R15.2, R17.2, R19.2, R21.2, R23.2, R25.2, R27.2, TP4.1, TP6.1, U1.3 (A2), U1.4 (A1), U1.5 (A0), U1.9 (VSS), U2.1 (ADDR), U2.3 (GND), U3.7 (GND), U4.1 (GND)
I2C_SCL: J3.5, J4.13, R2.2, U1.1 (SCL), U2.10 (SCL)
I2C_SDA: J3.4, J4.12, R1.2, U1.2 (SDA), U2.9 (SDA)
ISO0: R14.1, U3.3 (D1)
ISO1: R18.1, U3.6 (D2)
ISO2: R22.1, U3.8 (D3)
ISO3: R26.1, U3.11 (D4)
LCD_BL: J3.3, J4.11, R11.1
LCD_CS: J3.1, J4.8, R5.2
LCD_DC: J3.2, J4.9
LCD_MOSI: J4.5, R8.2
LCD_RST: J4.10, R6.2, U1.14 (GP2)
LCD_SCK: J4.6, R9.2
MCP_RST: R3.2, U1.6 (~RESET)
SD_CS: J4.7, R10.2
SPI_MISO: J2.6, J7.6
SPI_MOSI: J1.3, J6.3, R8.1
SPI_SCK: J1.4, J6.4, R9.1
TP_RST: J4.15, R7.2, U1.13 (GP1)

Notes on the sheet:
1 Ethernet / V6 - W5500
2 Zusaetzliche GPIOs
3 Messpunkte
4 Versorgung / Entkopplung
5 I2C-Portexpander / Reset
6 Pull-ups / Backlight-Pulldown
7 Display / Touch
8 SPI-Serienwiderstaende
VCC (3.3V)
3V3 (frei)
GND
MISO (frei)
MOSI
SCLK
SD_CS
LCD_CS
LCD_DC
LCD_RST
LCD_BL
TP_SDA
TP_SCL
TP_INT (frei)
TP_RST
Gleichnamige Netze sind auf diesem Blatt elektrisch verbunden.
23 x 41 mm / 2 Lagen / GH Side Entry / Touch-Betriebsart im ESP32 gespeichert
J6/J7: externe Gegenkontakte am W5500, keine weiteren PCB-Stecker.
J3 ist Adapterbelegung; V6-GPIOs vor Anschluss messen.
GPIO33 CS / 34 DC / 35 BL / 36 SDA / 37 SCL
VCC an J4.1 = 3.3V; J4.2 bleibt offen.
Touch per I2C-Polling (30 ms); kein TP_INT erforderlich.
Kein LCD-Readback, keine SD-Nutzung: MISO offen.
SD_CS mit Pull-up deaktiviert; 5V nur Reserve.
Kabel: GH15 beidseitig, elektrisch 1:1.
MCP23008: Adresse 0x20; Touch: 0x38.
R0 entfernbar zur Strommessung; kein Zusatzregler.
9 Spannungsmessung / ADC / Isolation
10 12V-Messanschluss, kein Versorgungseingang
11 Vier Messkanaele / Teiler und Filter
GP0 = ADC_ENABLE: Low -> Messwerte ungueltig.
AIN0 V6 3V3 / AIN1 EXT 3V3 / AIN2 5V / AIN3 12V

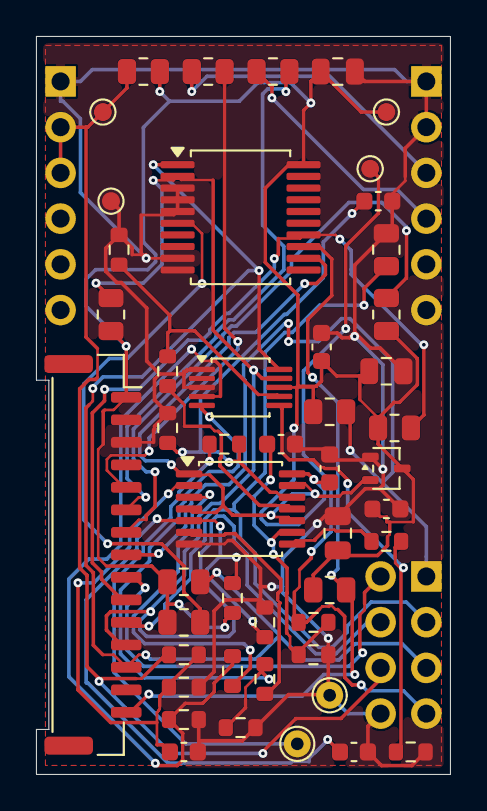
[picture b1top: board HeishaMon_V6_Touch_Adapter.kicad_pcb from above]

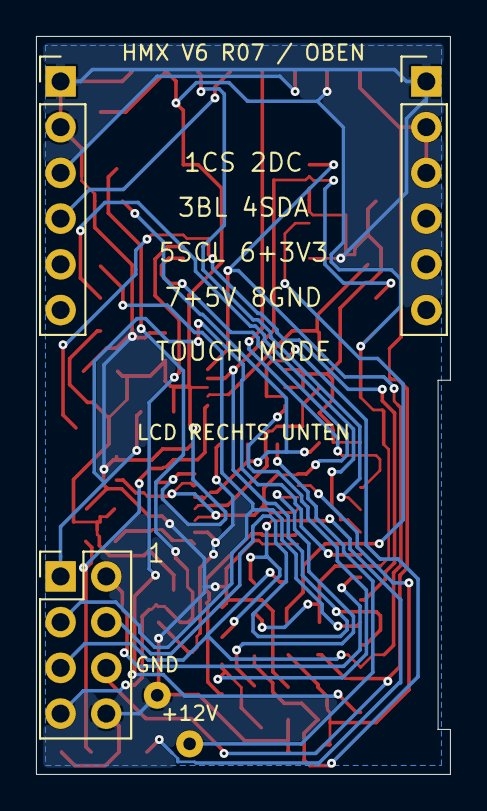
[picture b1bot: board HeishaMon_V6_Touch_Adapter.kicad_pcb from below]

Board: 2 copper layers, 23.0 x 41.0 mm, 51 parts (3 on the bottom side), 31 nets.
